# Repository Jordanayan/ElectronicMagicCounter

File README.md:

# ElectronicMagicCounter
Repository for all information regarding the Electronic Magic Counter project.

See https://scienceandpizza.com/2023/10/16/electronic-magic-counter/ for a full project write up

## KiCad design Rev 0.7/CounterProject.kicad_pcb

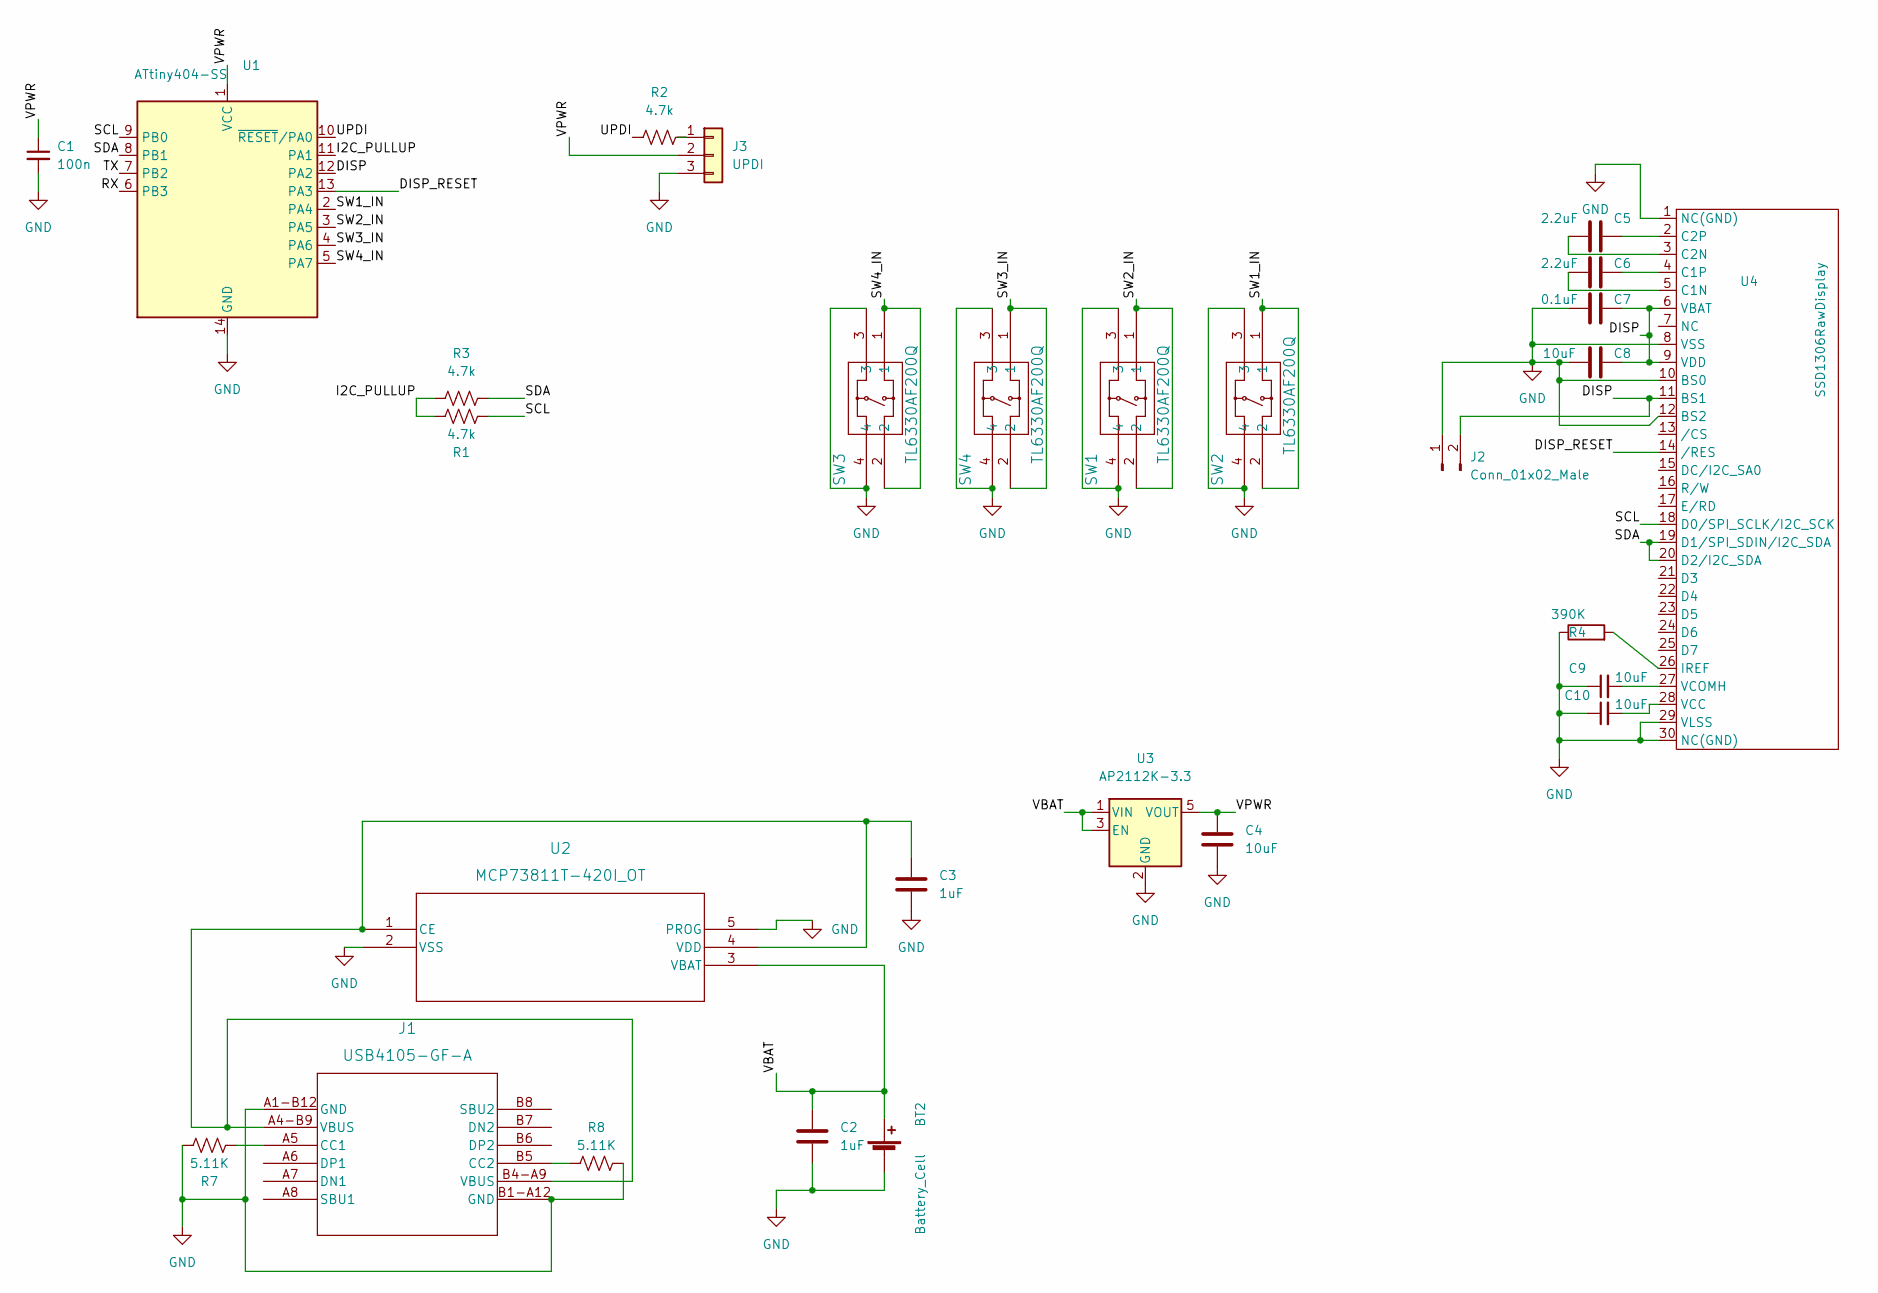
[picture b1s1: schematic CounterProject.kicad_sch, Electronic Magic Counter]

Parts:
BT2: Battery_Cell; JST_S2B-PH-K-S(LF)(SN)
C1: 100n; C_1206_3216Metric; JLCID C1525
C2, C3: 1uF; C_1206_3216Metric
C4, C8, C9, C10: 10uF; C_1206_3216Metric
C5, C6: 2.2uF; C_1206_3216Metric
C7: 0.1uF; C_1206_3216Metric
J1: USB4105-GF-A
J2: Conn_01x02_Male; C_0201_0603Metric
J3: UPDI; PinHeader_1x03_P2.54mm_Vertical
R1, R2, R3: 4.7k; R_1206_3216Metric
R4: 390K; R_1206_3216Metric
R7, R8: 5.11K; R_1206_3216Metric
SW1, SW2, SW3, SW4: TL6330AF200Q; TL6330_EWI
U1: ATtiny404-SS; SOIC-14_3.9x8.7mm_P1.27mm
U2: MCP73811T-420I_OT; SOT-23-5_MC_MCH
U3: AP2112K-3.3; SOT-23-5
U4: SSD1306RawDisplay

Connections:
/DISP: C7.2, C8.2, J2.2, U1.12 (PA2), U4.6 (VBAT), U4.9 (VDD), U4.11 (BS1)
/DISP_RESET: U1.13 (PA3), U4.14 (/RES)
/I2C_PULLUP: R1.2, R3.2, U1.11 (PA1)
/RX: U1.6 (PB3)
/SCL: R1.1, U1.9 (PB0), U4.18 (D0/SPI_SCLK/I2C_SCK)
/SDA: R3.1, U1.8 (PB1), U4.19 (D1/SPI_SDIN/I2C_SDA), U4.20 (D2/I2C_SDA)
/SW1_IN: SW2.1, SW2.2, U1.2 (PA4)
/SW2_IN: SW1.1, SW1.2, U1.3 (PA5)
/SW3_IN: SW4.1, SW4.2, U1.4 (PA6)
/SW4_IN: SW3.1, SW3.2, U1.5 (PA7)
/TX: U1.7 (PB2)
/UPDI: R2.1, U1.10 (~RESET/PA0)
/VBAT: BT2.1 (+), C2.1, U2.3 (VBAT), U3.1 (VIN), U3.3 (EN)
/VPWR: C1.1, C4.1, J3.2, U1.1 (VCC), U3.5 (VOUT)
GND: BT2.2 (-), C1.2, C2.2, C3.2, C4.2, C7.1, C8.1, C9.1, C10.1, J1.A1-B12 (GND), J1.B1-A12 (GND), J2.1, J3.3, R4.1, R7.2, R8.1, SW1.3, SW1.4, SW2.3, SW2.4, SW3.3, SW3.4, SW4.3, SW4.4, U1.14 (GND), U2.2 (VSS), U2.5 (PROG), U3.2 (GND), U4.1 (NC(GND)), U4.8 (VSS), U4.10 (BS0), U4.12 (BS2), U4.29 (VLSS), U4.30 (NC(GND))
unnamed: C3.1, J1.A4-B9 (VBUS), J1.B4-A9 (VBUS), U2.1 (CE), U2.4 (VDD)
unnamed: C5.1, U4.3 (C2N)
unnamed: C5.2, U4.2 (C2P)
unnamed: C6.1, U4.5 (C1N)
unnamed: C6.2, U4.4 (C1P)
unnamed: C9.2, U4.27 (VCOMH)
unnamed: C10.2, U4.28 (VCC)
unnamed: J1.A5 (CC1), R7.1
unnamed: J1.B5 (CC2), R8.2
unnamed: J3.1, R2.2
unnamed: R4.2, U4.26 (IREF)

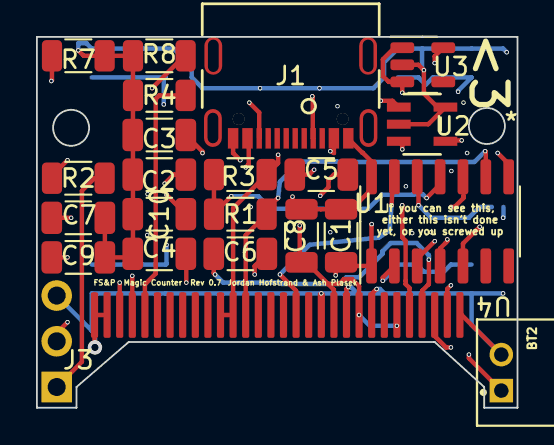
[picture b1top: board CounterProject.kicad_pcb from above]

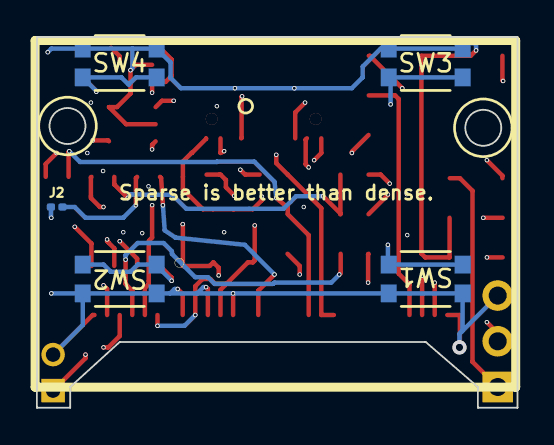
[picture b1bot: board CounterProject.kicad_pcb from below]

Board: 4 copper layers, 26.7 x 20.6 mm, 28 parts (5 on the bottom side), 24 nets.

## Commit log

2023-10-17 Add Board Design Files
2023-10-17 Added source code
2023-10-17 Added Step file of main housing

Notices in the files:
parts and their libraries:
Copyright 2016 Accelerated Designs. All rights reserved.
